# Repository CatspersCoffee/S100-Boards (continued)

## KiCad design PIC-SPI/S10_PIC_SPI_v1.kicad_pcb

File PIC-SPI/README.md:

# PIC-SPI

An S-100 interrupt and SPI board: an 8259A interrupt controller on the bus vectored-interrupt lines, an XC95288XL CPLD driving an SPI bus (DS1305 RTC, two MCP23S08 port expanders) and eight M25P80 SPI flash chips that can be loaded over USB (2016). The project name is `S100 PIC_SPI_v1`; the board carries no title text.

## Status
Built.

## Hardware

| Ref | Part | Role |
|---|---|---|
| U20 | XC95288XL-TQ144 | CPLD: S-100 bus logic, chip selects, SPI master, flash select, 7-segment data |
| U11 | 8259A | Interrupt controller on VI0*–VI7*, output to INT* |
| U22 | DS1305 + X2 + BAT1 (CR2032) | SPI real-time clock with battery backup |
| IC1, IC2 | MCP23S08 | SPI 8-bit port expanders, brought out on P13 "MCP_1" and P14 "MCP_2" |
| U14–U17, U23–U26 | M25P80 ×8 | 8 Mbit SPI flash each, one select line per chip from the CPLD |
| U18 | CH341A (12 MHz X1, USB Jx2) | USB-to-SPI bridge for loading the flash |
| U8 | PIC18F1330 | Switches the flash SPI bus between the CPLD and the CH341A |
| U12 | 74LV244 | Flash SPI bus switch, enabled by the PIC18F1330 |
| U3, U7 | 74LS682 | Address compare against DIP switches SW3 and SW5 (U7 → 8259 select) |
| U21 | 74LS240 | Inverts VI0*–VI7* to the 8259 IR0–IR7 inputs |
| U13 + SW6 | 74LS244 + DIP switch | Interrupt vector byte set by switch, put on the bus by the CPLD |
| U27, U28 + S1, S2 | 74HC4511 ×2 + 7-segment ×2 | Two-digit display driven by the CPLD |
| U4–U6, U19, U31, U3din1, U3dout1, U9, U10 | 74xx541 / 74HC245 | S-100 address, data and status buffers |
| U1, U2, Ux1 | 7805-type LDO, LM1086CS, 3.3 V SOT-223 | +5 V and 3.3 V from the S-100 +8 V rail |

- Board size: 254.0 × 134.1 mm (10.0 × 5.28 in), standard S-100 outline, 2 layers.
- KiCad: 2013-07-07 stable (BZR 4022); `.kicad_pcb` format version 3.
- Headers: P12 "Incomming Interrupt Channels" (jumpers route each VIx* line to 8259 IRx); JPx1–JPx8 "BOARD Interrupt Channel Selector" (picks the VIx* line for the board's own interrupt); JP1 (8259 INT to S-100 INT*); P19 "XILINX CABLE" (JTAG); P5 "PIC ISP"; P1 "FLASH ICP" (GND/CLK/Din/CS/Dout); P3 "EXT SPI"; P2 spare CPLD I/O.
- Switches: SW1 "RESET", SW2 "PIC RESET", SW50 "RUN/PROG"; DIP switches SW3, SW5 (address) and SW6 (interrupt vector).
- LEDs: "RUN", "PROG", "BS" (board select), "D0", "POWER", "POWER CH341A".

## How it works
- The CPLD sits behind buffered S-100 address (A0–A23), data (DI0–DI7, DO0–DO7) and status/control lines (sINP, sOUT, sMEMR, sM1, sINTA, sWO*, pDBIN, pWR*, MWRT, PHI, CLOCK*, RESET*, SLAVE_CLR*).
- Interrupts: incoming VI0*–VI7* reach the 8259A IR inputs through P12 jumpers and a 74LS240; the 8259A INT output goes to S-100 INT* (pin 73) through JP1. The 8259A chip select is decoded by U7 (CPLD pin 69 `in8259CS*`) and driven back out by the CPLD (pin 70 `out8259CS*`).
- The CPLD can also raise its own interrupt (pin 110 `BOARD_INTERRUPT_VECTb`) on any one VIx* line chosen with JPx1–JPx8, and can put a switch-set vector byte (SW6 via U13) on the data bus.
- SPI: CPLD pins 57/58/59 are SPI CLK/Din/Dout to the DS1305, both MCP23S08s and P3. Chip selects come from CPLD pins 25 (DS1305), 26/27 (IC1/IC2) and 17 (P3).
- Flash: the eight M25P80s share one SPI bus with a separate select each (CPLD pins 80–83 and 85–88). The 74LV244 connects that bus either to the CPLD or to the CH341A USB bridge; the PIC18F1330 controls which.
- The CPLD can also drive the S-100 bus-master request lines TMA0*–TMA3* and sXTRQ*.
- No CPLD project for this board is in the backups.

## Files
All files are in this folder:

| File | What it is |
|---|---|
| `S10_PIC_SPI_v1.sch` | Schematic (single sheet) |
| `S10_PIC_SPI_v1-cache.lib` | Symbol cache for the schematic |
| `S10_PIC_SPI_v1.kicad_pcb` | PCB layout |
| `S10_PIC_SPI_v1.net` | Netlist |
| `S10_PIC_SPI_v1.cmp` | Footprint assignments |
| `S10_PIC_SPI_v1.pro` | KiCad project |

## History
The git history replays the original dated KiCad backups, 3–10 January 2016. The first commit is the Flash-UART layout with its tracks removed, and the Flash-UART netlist and footprint files are carried over unchanged.

## Things to check (TODO)
- The P2 header silkscreen labels (P71–P78, P110–P116) are Flash-UART net names; on this board those pins go to CPLD pins 105–100 and 93–98.
- The final layout reports 1 unrouted connection.

## Credits
- Started from the user's own [Flash-UART](../Flash-UART) design.
- The S-100 edge connector symbol (`S100_MALE`) comes from the N8VEM KiCad library.
- John Monahan's 8259A test programs for his S100Computers.com PIC/RTC board (2010) were kept in the original project folder as reference. They are not included here.

## License
Hardware: CERN-OHL-S-2.0 for the original work in this folder; see the repo NOTICE for third-party parts.

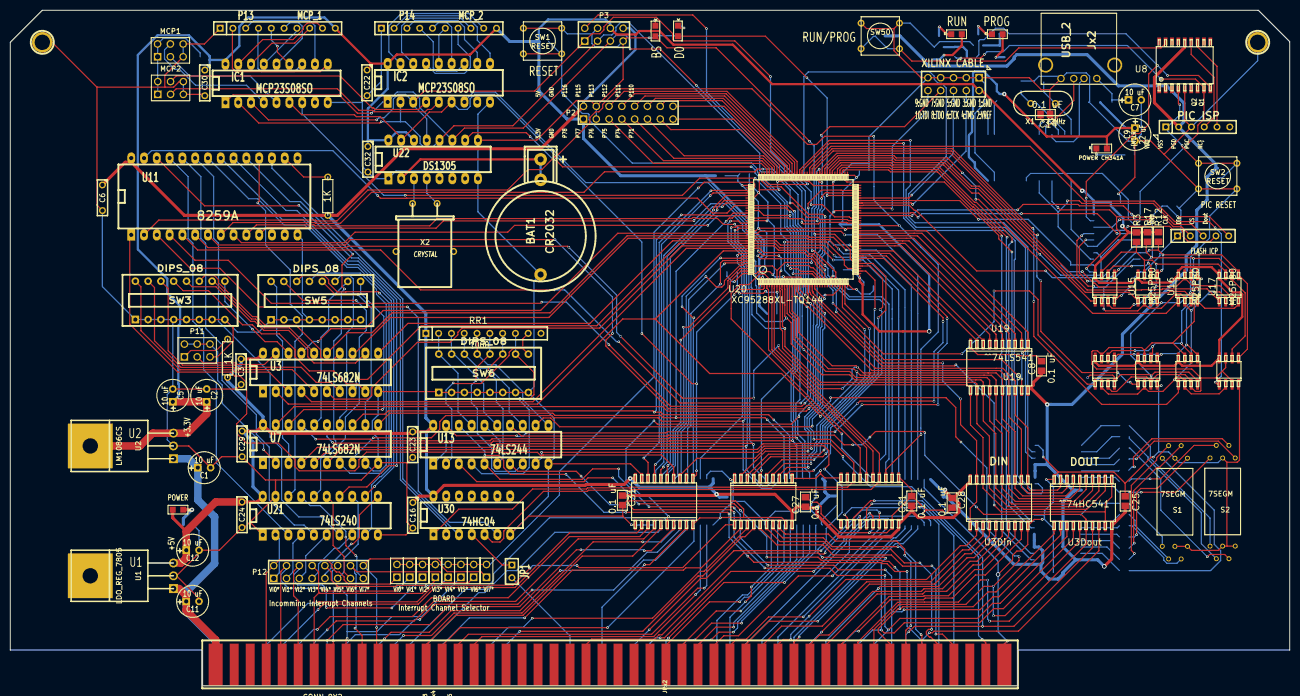
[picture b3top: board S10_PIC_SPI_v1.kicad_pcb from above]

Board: 2 copper layers, 254.0 x 134.1 mm, 163 parts (0 on the bottom side), 326 nets.

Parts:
BAT1: CR2032; ^^CR2032H
C1, C2, C5, C7, C11, C12: 10 uF; C1V7
C3, C6, C16, C22, C23, C24, C29, C30, C32: 0.1 uF; C2
C4, C8, C14, C17, C20, C21, C25, C27, C28, C31, C41, C42, C43: 0.1 uF; ^^SMD_Resistor-0805
C9: 22 uF; C1V7
C10, C18: 15 pF; ^^SMD_Resistor-0805
C13, C15: 0.01 uF; ^^SMD_Resistor-0805
C19, C26, C33, C34, C35, C36, C37, C38, C39, C40: C; ^^SMD_Resistor-0805
D1, D4: LED; ^^LED-0805
D5: POWER; ^^LED-0805
D7: BOARD_SELECT; ^^LED-0805
D8: POWER CH341A; ^^LED-0805
D9: D0; ^^LED-0805
IC1, IC2: MCP23S08SO; DIP-18__300_ELL
JP1: JUMPER; SIL-2
JPx1, JPx2, JPx3, JPx4, JPx5, JPx6, JPx7, JPx8: JUMPER; PIN_ARRAY_2X1
Jx2: USB_2; USB_A
MCP1, MCP2: CONN_3X2; PIN_ARRAY_3X2
P1: M25P80 ISP; SIL-5
P2: CONN_8X2; PIN_ARRAY_8x2
P3: EXT SPI; PIN_ARRAY_4X2
P4: S100_MALE
P5: PIC_ISP; SIL-6
P6, P7: CONN_1; 1pin
P8, P9: CONN_2; ^^SMD_Resistor-0805
P11: CONN_3X2; PIN_ARRAY_3X2
P12: CONN_8X2; pin_array_8x2
P13: MCP_1; SIL-10
P14: MCP_2; SIL-10
P19: XILINX CABLE2; PIN_ARRAY_5x2
Q1, Q2: ^^NPN-SOT23; ^^-SOT23
R1, R5, R14, R15, R20, R21, R29: 330; ^^SMD_Resistor-0805
R2, R18, R19, R28: 470; ^^SMD_Resistor-0805
R3, R31, R32, R33, R34, R35, R36, R37, R38, R39, R40, R41, R42, R43, R44: 1K; ^^SMD_Resistor-0805
R4, R8, R10, R30: 10k; ^^SMD_Resistor-0805
R6, R11: 1K; ^^R3
R7: 50; ^^SMD_Resistor-0805
R9, R12, R17: 10K; ^^SMD_Resistor-0805
R25, R26, R27: 100; ^^SMD_Resistor-0805
RR1: 1000; r_pack9
S1, S2: 7SEGM; ^^VQB71_7segment
SW1, SW2: RESET; SW_PUSH_SMALL
SW3, SW5, SW6: DIPS_08; SWDIP8
SW50: FLASH/RUN; SW_PUSH_SMALL
U1: LDO_REG_7805; ^^TO220
U2: LM1086CS; ^^TO220
U3, U7: 74LS682N; DIP-20__300_ELL
U3din1, U3dout1: ^^74HC541; ^^-SO20W
U4, U5, U6, U19, U31: ^^74LS541; ^^-SO20W
U8: PIC18F1330; -SO18-1
U9, U10: 74HC245; ^^-SO20W
U11: 8259A; DIP-28__600_ELL
U12: ^^74LV244; ^^-SO20W
U13: 74LS244; DIP-20__300_ELL
U14, U15, U16, U17, U23, U24, U25, U26: M25P80; -SO8
U18: CH341A; ^^-SO28W
U20: XC95288XL-TQ144; -TQFP144
U21: 74LS240; DIP-20__300_ELL
U22: DS1305; DIP-16__300_ELL
U27, U28: 74HC4511; ^^-SO16W
U30: 74HC04; DIP-14__300_ELL
Ux1: ^^3.3VREG_SOT223; -SOT223
X1: 12MHz; Crystal_HC-49U_Vert
X2: CRYSTAL; Crystal_HC-49U_Horiz

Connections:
/7SEG_0_D0: U20.74, U27.7
/7SEG_0_D1: U20.75, U27.1
/7SEG_0_D2: U20.76, U27.2
/7SEG_0_D3: U20.77, U27.6
/7SEG_1_D0: U20.106, U28.7
/7SEG_1_D1: U20.107, U28.1
/7SEG_1_D2: U20.91, U28.2
/7SEG_1_D3: U20.92, U28.6
/25Pxx_CS: U12.5, U12.14, U20.79
/25Pxx_SEL_0: U14.1, U20.80
/25Pxx_SEL_1: U15.1, U20.81
/25Pxx_SEL_2: U16.1, U20.82
/25Pxx_SEL_3: U17.1, U20.83
/25Pxx_SEL_4: U20.85, U23.1
/25Pxx_SEL_5: U20.86, U24.1
/25Pxx_SEL_6: U20.87, U25.1
/25Pxx_SEL_7: U20.88, U26.1
/+8V: C1.1, C11.1, P4.1, P4.51, U1.1, U2.1
//M1: U9.2, U20.43
/A0: P4.79, U4.2
/A0b: U4.18, U11.27, U20.117
/A1: P4.80, U4.3
/A1b: U4.17, U7.17, U20.118
/A2: P4.81, U4.4
/A2b: U4.16, U7.15, U20.119
/A3: P4.31, U4.5
/A3b: U4.15, U7.13, U20.120
/A4: P4.30, U4.6
/A4b: U4.14, U7.11, U20.121
/A5: P4.29, U4.7
/A5b: U4.13, U7.8, U20.124
/A6: P4.82, U4.8
/A6b: U4.12, U7.6, U20.125
/A7: P4.83, U4.9
/A7b: U4.11, U7.4, U20.126
/A8: P4.84, U5.2
/A8b: U3.17, U5.18, U20.128
/A9: P4.34, U5.3
/A9b: U3.15, U5.17, U20.129
/A10: P4.37, U5.4
/A10b: U3.13, U5.16, U20.130
/A11: P4.87, U5.5
/A11b: U3.11, U5.15, U20.131
/A12: P4.33, U5.6
/A12b: U3.8, U5.14, U20.132
/A13: P4.85, U5.7
/A13b: U3.6, U5.13, U20.133
/A14: P4.86, U5.8
/A14b: U3.4, U5.12, U20.134
/A15: P4.32, U5.9
/A15b: U3.2, U5.11, U20.135
/A16: P4.16, U6.2
/A16b: U6.18, U20.136
/A17: P4.17, U6.3
/A17b: U6.17, U20.137
/A18: P4.15, U6.4
/A18b: U6.16, U20.138
/A19: P4.59, U6.5
/A19b: U6.15, U20.139
/A20: P4.61, U6.6
/A20b: U6.14, U20.140
/A21: P4.62, U6.7
/A21b: U6.13, U20.142
/A22: P4.63, U6.8
/A22b: U6.12, U20.143
/A23: P4.64, U6.9
/A23b: U6.11, U20.116
/BOARD_INTERRUPT_VECTb: JPx1.2, JPx2.2, JPx3.2, JPx4.2, JPx5.2, JPx6.2, JPx7.2, JPx8.2, U20.110
/BOARD_SEL_LED: D7.1, U20.31
/CLOCK*: P4.49, U10.13
/CLOCK*b: U10.7, U20.5
/CPLD2_TCK: R25.1, U20.67
/CPLD2_TDI: R26.1, U20.63
/CPLD2_TDO: P19.8, U20.122
/CPLD2_TMS: R27.1, U20.65
/CPLD_45: U19.9, U20.45
/CPLD_46: U19.8, U20.46
/CPLD_48: U19.7, U20.48
/CPLD_49: U19.6, U20.49
/CPLD_68: D9.1, U20.68
/CPLD_71: P2.15, U20.100
/CPLD_74: P2.13, U20.101
/CPLD_75: P2.11, U20.102
/CPLD_76: P2.9, U20.103
/CPLD_77: P2.7, U20.104
/CPLD_78: P2.5, U20.105
/CPLD_110: P2.16, U20.98
/CPLD_111: P2.14, U20.97
/CPLD_112: P2.12, U20.96
/CPLD_113: P2.10, U20.95
/CPLD_115: P2.8, U20.94
/CPLD_116: P2.6, U20.93
/CPLD_130: U19.5, U20.50
/CPLD_131: U19.4, U20.51
/CPLD_132: U19.3, U20.52
/CPLD_133: U19.2, U20.53
/CPLD_134: U19.1, U19.19, U20.54
/CPLD_M25P80_CLK: U12.2, U20.60
/CPLD_M25P80_CS: U12.6, U20.64
/CPLD_M25P80_Din: U12.4, U20.61
/CPLD_M25P80_Dout: R9.2, U12.12, U20.66
/D0: U3din1.18, U3dout1.2, U11.11, U19.11, U20.9
/D1: U3din1.17, U3dout1.3, U11.10, U19.12, U20.10
/D2: U3din1.16, U3dout1.4, U11.9, U19.13, U20.11
/D3: U3din1.15, U3dout1.5, U11.8, U19.14, U20.12
/D4: U3din1.14, U3dout1.6, U11.7, U19.15, U20.13
/D5: U3din1.13, U3dout1.7, U11.6, U19.16, U20.14
/D6: U3din1.12, U3dout1.8, U11.5, U19.17, U20.15
/D7: U3din1.11, U3dout1.9, U11.4, U19.18, U20.16
/DBUSIN_EN: U3din1.1, U3din1.19, U20.22
/DBUSOUT_EN: U3dout1.1, U3dout1.19, U20.21
/DI0: P4.95, U3dout1.18, U13.18
/DI1: P4.94, U3dout1.17, U13.16
/DI2: P4.41, U3dout1.16, U13.14
/DI3: P4.42, U3dout1.15, U13.12
/DI4: P4.91, U3dout1.14, U13.9
/DI5: P4.92, U3dout1.13, U13.7
/DI6: P4.93, U3dout1.12, U13.5
/DI7: P4.43, U3dout1.11, U13.3
/DO0: P4.36, U3din1.2
/DO1: P4.35, U3din1.3
/DO2: P4.88, U3din1.4
/DO3: P4.89, U3din1.5
/DO4: P4.38, U3din1.6
/DO5: P4.39, U3din1.7
/DO6: P4.40, U3din1.8
/DO7: P4.90, U3din1.9
/INT*: JP1.2, P4.73
/IOREQb: P4.69, U9.14
/IOREQbb: U9.6, U20.39
/M2_MCLR: P5.1, R4.2, SW2.1, U8.4
/M2_PGC: P5.5, U8.12
/M2_PGD: P5.4, U8.13
/MCP1_0: IC1.10, P13.2
/MCP1_1: IC1.11, P13.3
/MCP1_2: IC1.12, P13.4
/MCP1_3: IC1.13, P13.5
/MCP1_4: IC1.14, P13.6
/MCP1_5: IC1.15, P13.7
/MCP1_6: IC1.16, P13.8
/MCP1_7: IC1.17, P13.9
/MCP2_0: IC2.10, P14.2
/MCP2_1: IC2.11, P14.3
/MCP2_2: IC2.12, P14.4
/MCP2_3: IC2.13, P14.5
/MCP2_4: IC2.14, P14.6
/MCP2_5: IC2.15, P14.7
/MCP2_6: IC2.16, P14.8
/MCP2_7: IC2.17, P14.9
/MCP_AddrHi: MCP1.1, MCP1.2, MCP2.1, MCP2.2, R7.1
/MWRT: P4.68, U9.13
/MWRTb: U9.7, U20.40
/NDEF2: P4.65, U9.12
/NDEF2b: U9.8, U20.41
/PHI: P4.24, U10.14
/PHIb: U10.6, U20.4
/PROG_M25P80_CLK: P1.2, U12.11, U18.18
/PROG_M25P80_CS: P1.4, U12.15, U18.15
/PROG_M25P80_Din: P1.3, U12.13, U18.20
/PROG_M25P80_Dout: P1.5, R10.2, U12.3, U18.22
/Q1: R2.2, R18.2, U8.9, U12.19
/Q2: R19.2, R28.2, U8.8, U12.1
/RESET*: P4.75, U31.9
/RESET*b: IC1.6, IC2.6, U20.3, U22.15, U31.11
/SLAVE_CLR*: P4.54, U9.11
/SLAVE_CLR*vv: U9.9, U20.33
/SPI_CLK: IC1.1, IC2.1, P3.5, U20.57, U22.11
/SPI_CS_00: U20.25, U22.10
/SPI_CS_01: IC1.7, U20.26
/SPI_CS_02: IC2.7, U20.27
/SPI_CS_03: P3.2, U20.17
/SPI_Din: IC1.2, IC2.2, P3.3, U20.58, U22.12
/SPI_Dout: IC1.3, IC2.3, P3.1, U20.59, U22.13
/TMA0*: P4.55, U31.2
/TMA0_CPLD: U20.111, U31.18
/TMA1*: P4.56, U31.3
/TMA1_CPLD: U20.112, U31.17
/TMA2*: P4.57, U31.4
/TMA2_CPLD: U20.113, U31.16
/TMA3*: P4.14, U31.5
/TMA3_CPLD: U20.115, U31.15
/USB_VCC1: C7.1, Jx2.1, Ux1.3
/V3.3: C2.1, C4.1, C5.1, C22.1, C30.1, C32.1, IC1.18, IC2.18, P2.1, P3.6, P8.2, P9.2, P13.10, P14.10, P19.2, R3.2, R7.2, R8.1, R12.1, R17.1, U2.3, U2.4, U12.20, U14.8, U15.8, U16.8, U17.8, U22.14, U22.16, U23.8, U24.8, U25.8, U26.8
/V3.3_CLPD_INT: C26.1, C33.1, P8.1, U20.8, U20.42, U20.84, U20.141
/V3.3_CLPD_IO: C19.1, C34.1, C35.1, C36.1, C37.1, C38.1, C39.1, C40.1, P9.1, U20.1, U20.37, U20.55, U20.73, U20.109, U20.127
/V3.3b: C9.1, C13.2, C15.1, D8.1, U18.28, Ux1.2
/VI0: U11.18, U21.18
/VI0*: JPx1.1, P4.4, P12.2
/VI1: U11.19, U21.16
/VI1*: JPx2.1, P4.5, P12.4
/VI2: U11.20, U21.14
/VI2*: JPx3.1, P4.6, P12.6
/VI3: U11.21, U21.12
/VI3*: JPx4.1, P4.7, P12.8
/VI4: U11.22, U21.9
/VI4*: JPx5.1, P4.8, P12.10
/VI5: U11.23, U21.7
/VI5*: JPx6.1, P4.9, P12.12
/VI6: U11.24, U21.5
/VI6*: JPx7.1, P4.10, P12.14
/VI7: U11.25, U21.3
/VI7*: JPx8.1, P4.11, P12.16
/Vbat: BAT1.1, U22.2
/Z80intVectorBusout: U13.1, U13.19, U20.44
/in8259CS*: U7.19, U20.69
/out8259CS*: U20.70, U31.6
/out8259CS*bufferedViaU31: U11.1, U31.14
/pDBIN: P4.78, U10.16
/pDBIN*b: U11.3, U30.6
/pDBINb: U10.4, U20.7, U30.5
/pWR*: P4.77, U10.17
/pWR*b: U10.3, U11.2, U20.56
/sINP: P4.46, U9.16
/sINPb: U9.4, U20.35
/sINTA: P4.96, U10.12
/sINTA*b: U11.26, U30.2
/sINTAb: U10.8, U20.20, U30.1
/sM1: P4.44, U9.18
/sMEMR: P4.47, U9.15
/sMEMRb: U9.5, U20.38
/sOUT: P4.45, U9.17
/sOUTb: U9.3, U20.34
/sWO*: P4.97, U10.15
/sWO*b: U10.5, U20.6
/sXTRQ*: P4.58, U31.7
/sXTRQ*b: U20.23, U31.13
GND: BAT1.2, C1.2, C2.2, C3.2, C4.2, C5.2, C6.2, C7.2, C8.2, C9.2, C10.2, C11.2, C12.2, C14.1, C15.2, C16.2, C17.2, C18.2, C19.2, C20.2, C21.2, C22.2, C23.2, C24.2, C25.2, C26.2, C27.2, C28.2, C29.2, C30.2, C31.2, C32.2, C33.2, C34.2, C35.2, C36.2, C37.2, C38.2, C39.2, C40.2, C41.2, C42.2, C43.2, IC1.9, IC2.9, Jx2.4, MCP1.5, MCP1.6, MCP2.5, MCP2.6, P1.1, P2.3, P2.4, P3.4, P3.7, P4.50, P4.100, P5.3, P6.1, P7.1, P11.5, P13.1, P14.1, P19.1, P19.3, P19.5, P19.7, P19.9, Q1.2, Q2.2, R5.2, R9.1, R10.1, R14.2, R15.1, R20.1, R21.1, S1.3, S1.5, S1.8, S2.3, S2.5, S2.8, SW1.1, SW2.2, SW3.1, SW3.2, SW3.3, SW3.4, SW3.5, SW3.6, SW3.7, SW3.8, SW5.1, SW5.2, SW5.3, SW5.4, SW5.5, SW5.6, SW5.7, SW5.8, SW6.1, SW6.2, SW6.3, SW6.4, SW6.5, SW6.6, SW6.7, SW6.8, SW50.1, U1.2, U2.2, U3.10, U3din1.10, U3dout1.10, U4.1, U4.10, U4.19, U5.1, U5.10, U5.19, U6.1, U6.10, U6.19, U7.10, U8.5, U9.1, U9.10, U9.19, U10.1, U10.10, U10.19, U11.14, U12.10, U13.10, U14.4, U15.4, U16.4, U17.4, U18.12, U18.27, U19.10, U20.18, U20.29, U20.36, U20.47, U20.62, U20.72, U20.89, U20.90, U20.99, U20.108, U20.114, U20.123, U20.144, U21.1, U21.10, U21.19, U22.1, U22.8, U22.9, U23.4, U24.4, U25.4, U26.4, U27.8, U28.8, U30.7, U31.1, U31.10, U31.19, Ux1.1
unnamed: P12.7, U21.8
unnamed: P12.9, U21.11
unnamed: P12.11, U21.13
unnamed: P12.13, U21.15
unnamed: P12.15, U21.17
unnamed: P12.5, U21.6
unnamed: P12.1, U21.2
unnamed: P12.3, U21.4
unnamed: RR1.5, SW6.13, U13.11
unnamed: RR1.4, SW6.14, U13.13
unnamed: RR1.3, SW6.15, U13.15
unnamed: P11.3, U3.19
unnamed: RR1.7, SW6.11, U13.6
unnamed: RR1.8, SW6.10, U13.4
unnamed: RR1.6, SW6.12, U13.8
unnamed: RR1.2, SW6.16, U13.17
unnamed: RR1.9, SW6.9, U13.2
unnamed: SW3.11, U3.14
unnamed: SW3.12, U3.12
unnamed: SW3.13, U3.9
unnamed: SW3.14, U3.7
unnamed: SW3.15, U3.5
unnamed: SW3.16, U3.3
unnamed: SW3.10, U3.16
unnamed: SW3.9, U3.18
unnamed: JP1.1, U30.4
unnamed: IC2.4, MCP2.4
unnamed: IC1.5, MCP1.3
unnamed: IC1.4, MCP1.4
unnamed: IC2.5, MCP2.3
unnamed: SW5.9, U7.18
unnamed: SW5.10, U7.16
unnamed: SW5.11, U7.14
unnamed: SW5.12, U7.12
unnamed: SW5.13, U7.9
unnamed: SW5.14, U7.7
unnamed: SW5.15, U7.5
unnamed: SW5.16, U7.3
unnamed: U22.3, X2.1
unnamed: U22.4, X2.2
unnamed: P11.2, P11.4, P11.6, U7.2
unnamed: D1.2, Q1.3
unnamed: D9.2, R21.2
unnamed: D4.2, Q2.3
unnamed: Jx2.3, U18.10
unnamed: C10.1, U18.13, X1.1
unnamed: C18.1, U18.14, X1.2
unnamed: Jx2.2, U18.11
unnamed: R15.2, U18.1
unnamed: D8.2, R14.1
unnamed: R8.2, SW1.2, U20.24
unnamed: R36.1, S1.9
unnamed: R31.1, S1.7
unnamed: R32.1, S1.6
unnamed: R33.1, S1.4
unnamed: R34.1, S1.2
unnamed: R35.1, S1.1
unnamed: R37.1, S1.10
unnamed: R38.1, S2.7
unnamed: R39.1, S2.6
unnamed: R40.1, S2.4
unnamed: R41.1, S2.2
unnamed: R42.1, S2.1
unnamed: R43.1, S2.9
unnamed: R44.1, S2.10
unnamed: R42.2, U28.9
unnamed: R37.2, U27.14
unnamed: R31.2, U27.13
unnamed: R32.2, U27.12
unnamed: R33.2, U27.11
unnamed: R34.2, U27.10
unnamed: R35.2, U27.9
unnamed: R36.2, U27.15
unnamed: R38.2, U28.13
unnamed: R39.2, U28.12
unnamed: R40.2, U28.11
unnamed: R41.2, U28.10
unnamed: R43.2, U28.15
unnamed: R44.2, U28.14
unnamed: D7.2, R20.2
unnamed: C14.2, U18.9
unnamed: C13.1, U18.2
unnamed: P11.1, R11.2
unnamed: U11.17, U30.3
unnamed: R6.1, U11.16
unnamed: D1.1, R1.1
unnamed: R3.1, U14.3, U14.7, U15.3, U15.7, U16.3, U16.7, U17.3, U17.7, U23.3, U23.7, U24.3, U24.7, U25.3, U25.7, U26.3, U26.7
unnamed: D4.1, R29.1
unnamed: P19.10, R26.2
unnamed: P19.6, R25.2
unnamed: P19.4, R27.2
unnamed: D5.2, R5.1
unnamed: R30.2, SW50.2, U8.17
unnamed: R17.2, U12.9, U12.18, U14.6, U15.6, U16.6, U17.6, U23.6, U24.6, U25.6, U26.6
unnamed: Q1.1, R2.1, R19.1
unnamed: Q2.1, R18.1, R28.1
unnamed: R12.2, U12.7, U12.16, U14.5, U15.5, U16.5, U17.5, U23.5, U24.5, U25.5, U26.5
unnamed: U12.8, U12.17, U14.2, U15.2, U16.2, U17.2, U23.2, U24.2, U25.2, U26.2
VCC: C3.1, C6.1, C8.1, C12.1, C16.1, C17.1, C20.1, C21.1, C23.1, C24.1, C25.1, C27.1, C28.1, C29.1, C31.1, C41.1, C42.1, C43.1, D5.1, P2.2, P3.8, P5.2, R1.2, R4.1, R6.2, R11.1, R29.2, R30.1, RR1.1, U1.3, U3.20, U3din1.20, U3dout1.20, U4.20, U5.20, U6.20, U7.20, U8.14, U9.20, U10.20, U11.28, U13.20, U19.20, U21.20, U27.3, U27.4, U27.5, U27.16, U28.3, U28.4, U28.5, U28.16, U30.14, U31.20

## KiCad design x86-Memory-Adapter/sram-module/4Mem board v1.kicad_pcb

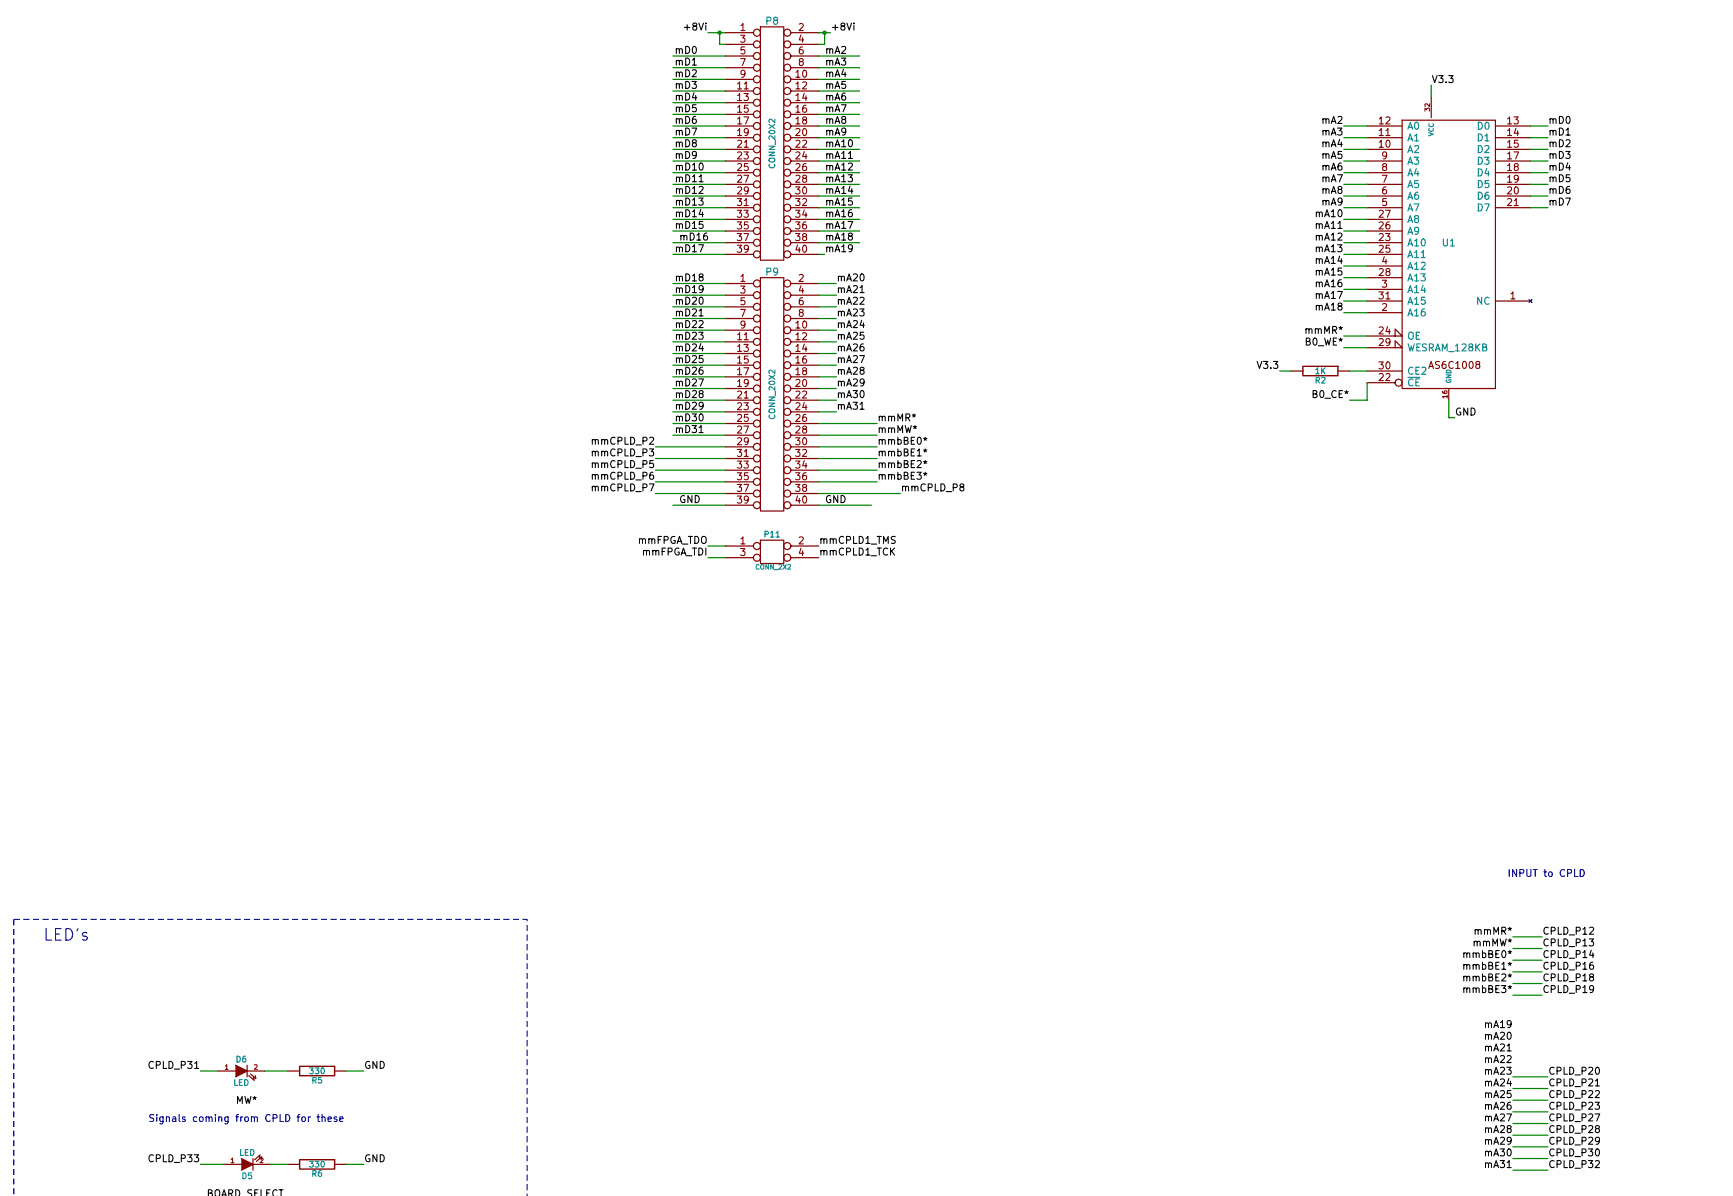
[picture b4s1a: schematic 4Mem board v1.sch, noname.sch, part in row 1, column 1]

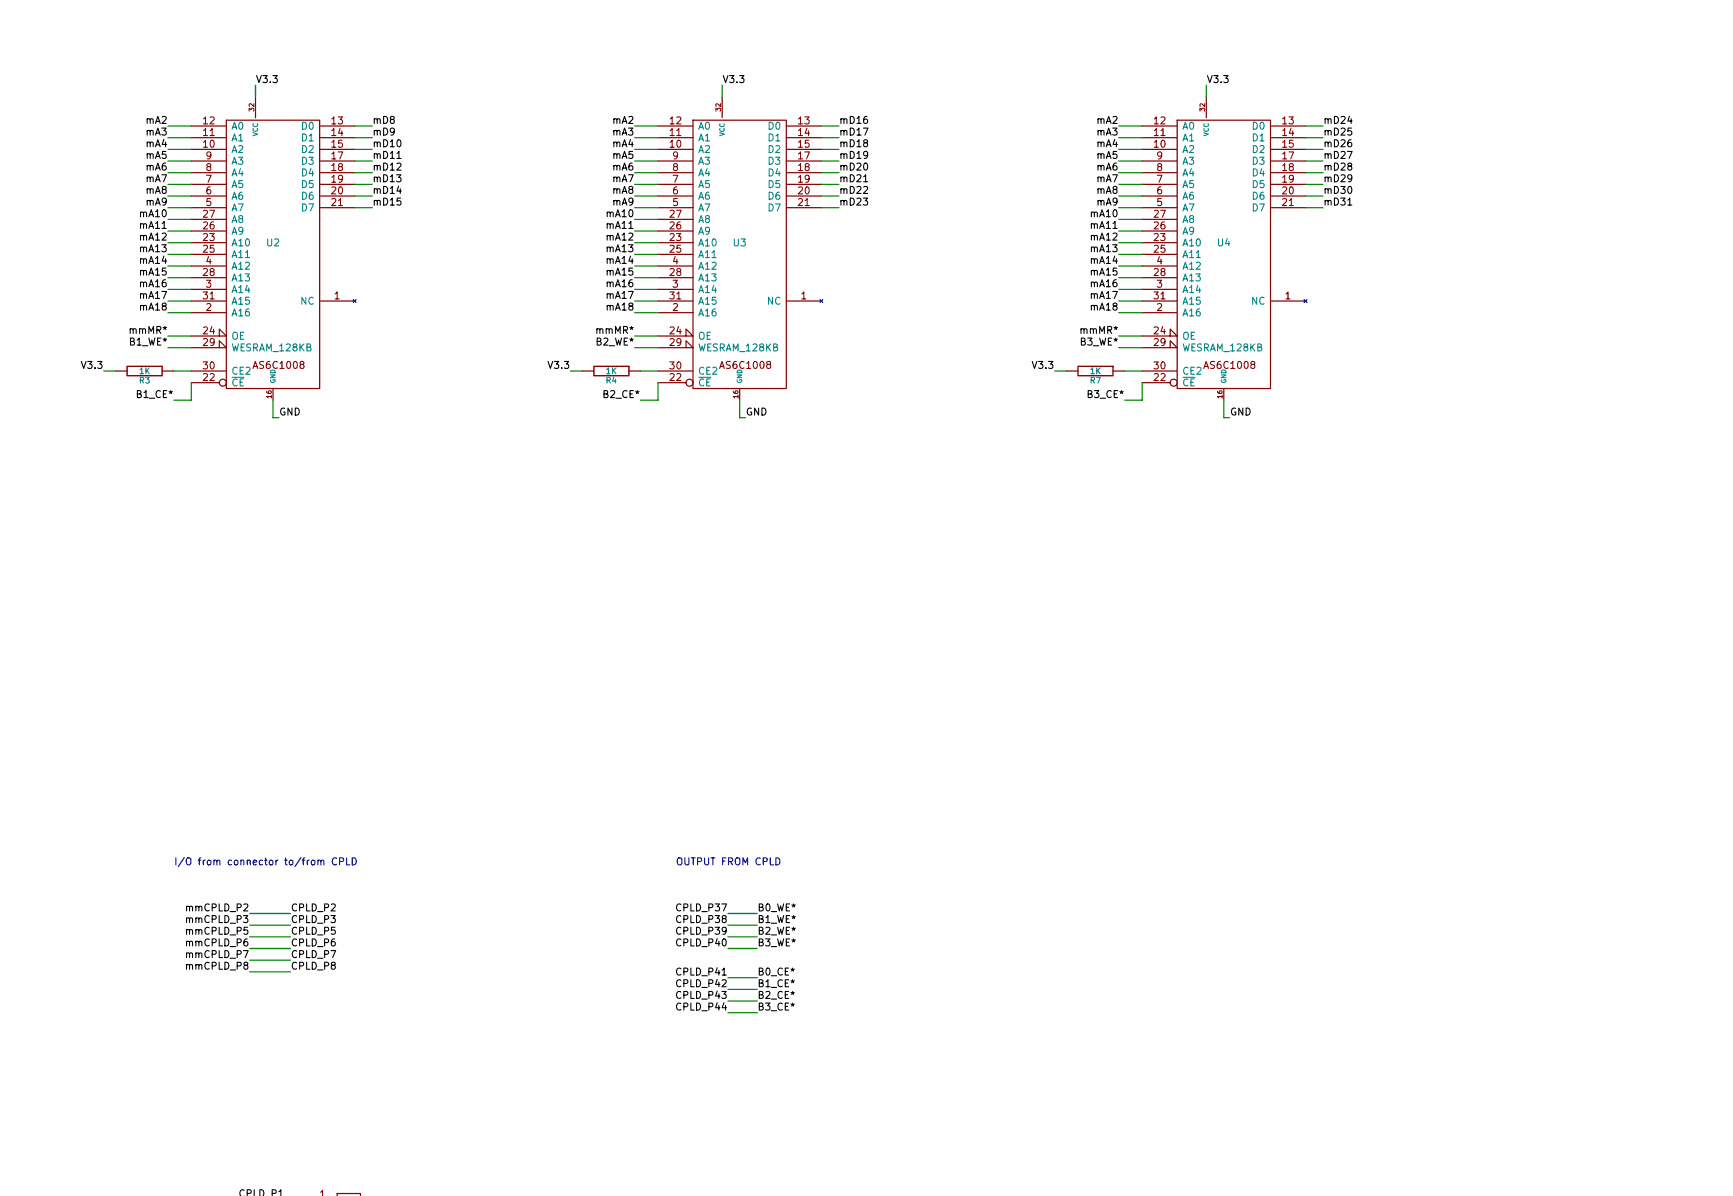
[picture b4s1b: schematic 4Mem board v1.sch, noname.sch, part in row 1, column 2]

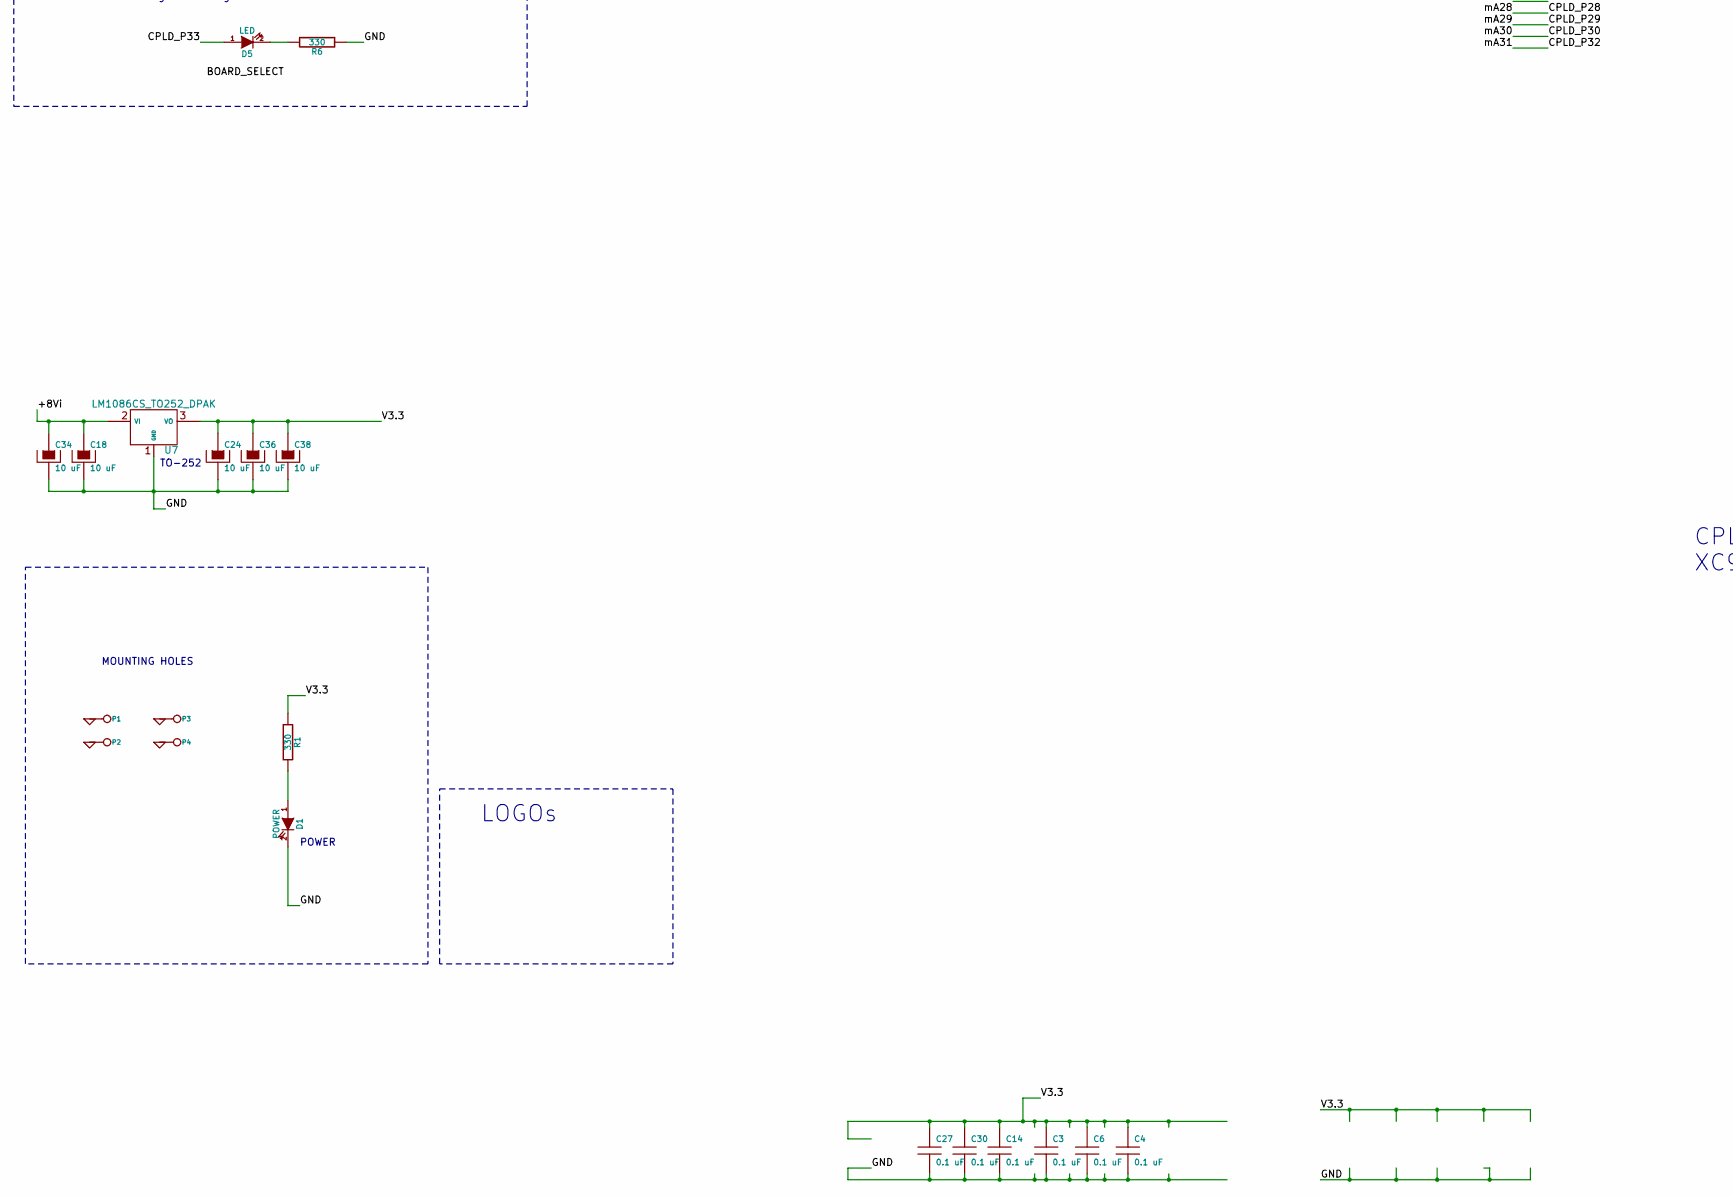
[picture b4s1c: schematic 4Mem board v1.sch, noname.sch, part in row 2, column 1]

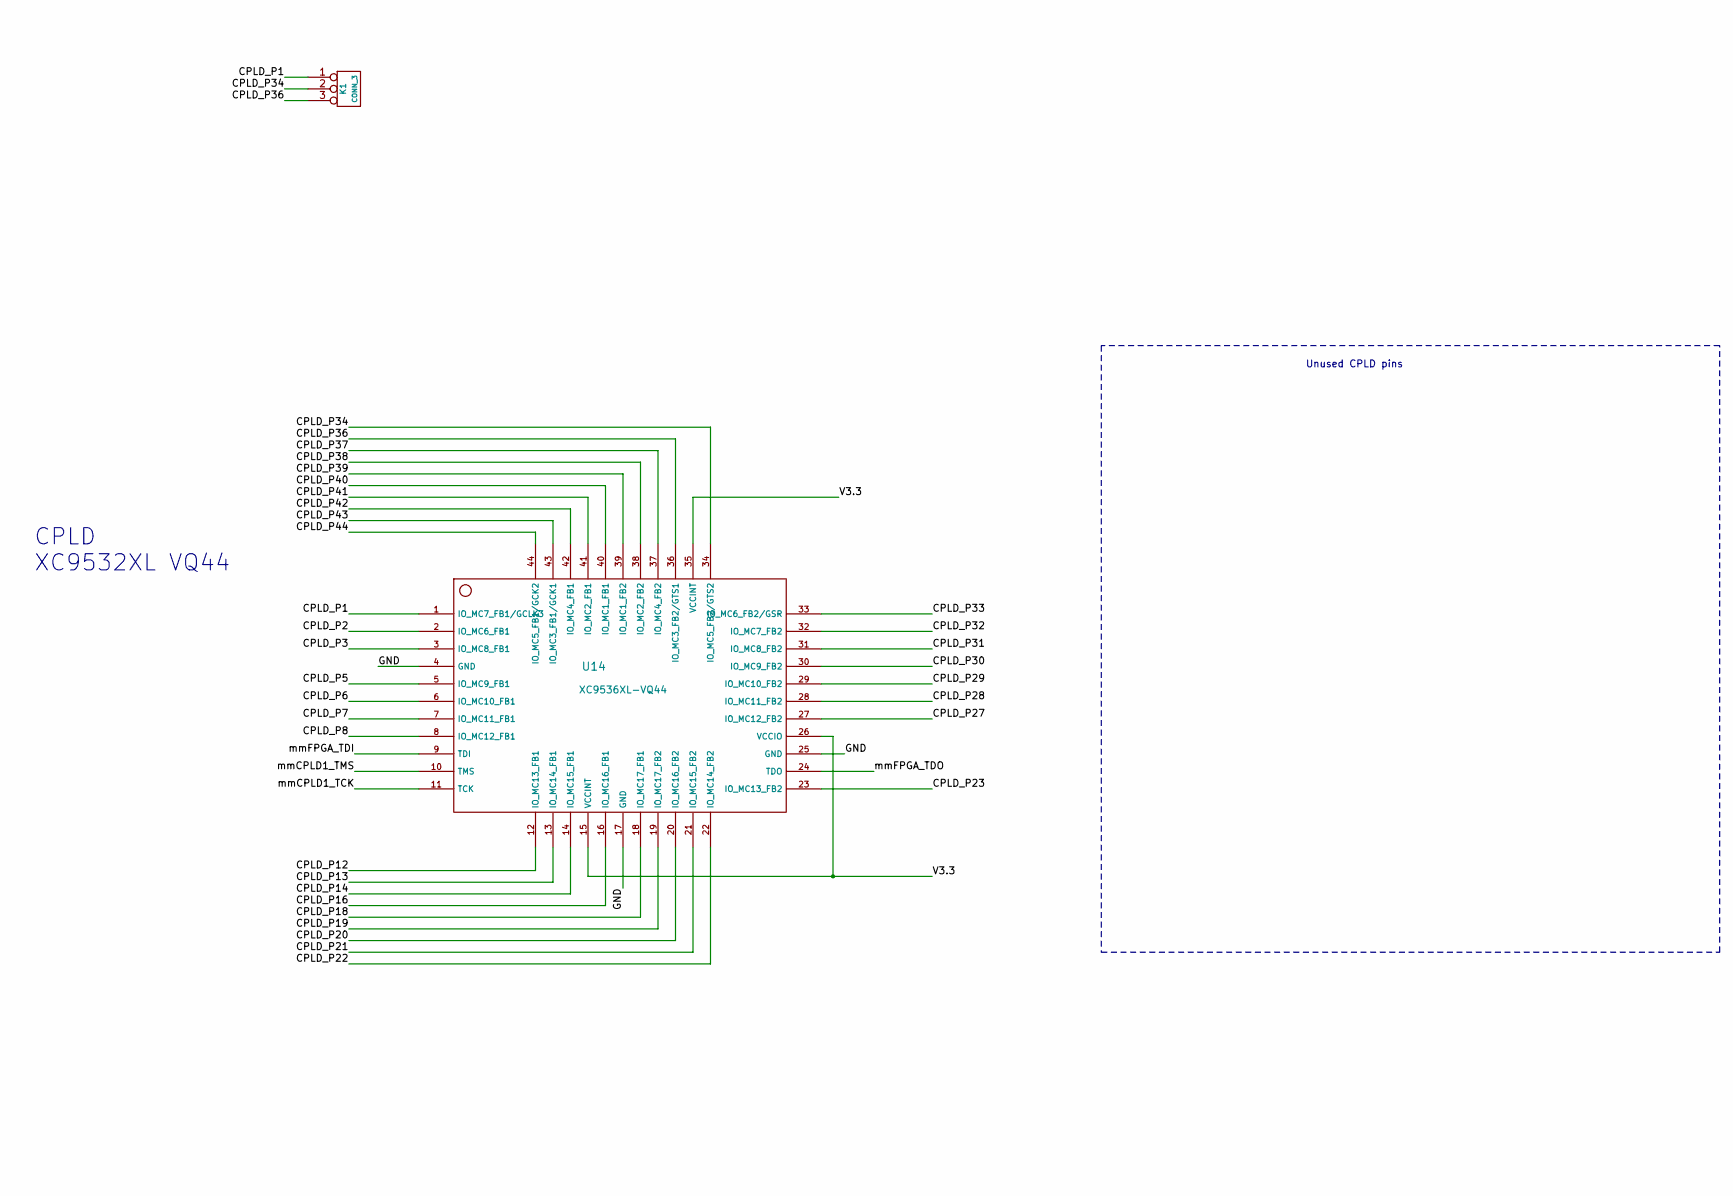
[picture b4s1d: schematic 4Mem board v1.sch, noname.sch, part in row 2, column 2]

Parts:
C3, C4, C6, C14: 0.1 uF; C2
C18, C24, C34, C36, C38: 10 uF
C27, C30: 0.1 uF
D1: POWER
D5, D6: LED; LEDV
K1: CONN_3
P1, P2, P3, P4: CONN_1
P8, P9: CONN_20X2; 8MB_SRAM
P11: CONN_2X2
R1, R5, R6: 330
R2, R3, R4, R7: 1K
U1, U2, U3, U4: SRAM_128KB
U7: LM1086CS_TO252_DPAK
U14: XC9536XL-VQ44

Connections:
/+8Vi: C18.1, C34.1, P8.1, P8.2, P8.3, P8.4, U7.2 (VI)
/B0_CE*: U1.22 (~CE), U14.41 (IO_MC2_FB1)
/B0_WE*: U1.29 (WE), U14.37 (IO_MC4_FB2)
/B1_CE*: U2.22 (~CE), U14.42 (IO_MC4_FB1)
/B1_WE*: U2.29 (WE), U14.38 (IO_MC2_FB2)
/B2_CE*: U3.22 (~CE), U14.43 (IO_MC3_FB1/GCK1)
/B2_WE*: U3.29 (WE), U14.39 (IO_MC1_FB2)
/B3_CE*: U4.22 (~CE), U14.44 (IO_MC5_FB1/GCK2)
/B3_WE*: U4.29 (WE), U14.40 (IO_MC1_FB1)
/CPLD_P1: K1.1, U14.1 (IO_MC7_FB1/GCLK3)
/CPLD_P2: P9.29, U14.2 (IO_MC6_FB1)
/CPLD_P3: P9.31, U14.3 (IO_MC8_FB1)
/CPLD_P5: P9.33, U14.5 (IO_MC9_FB1)
/CPLD_P6: P9.35, U14.6 (IO_MC10_FB1)
/CPLD_P7: P9.37, U14.7 (IO_MC11_FB1)
/CPLD_P8: P9.38, U14.8 (IO_MC12_FB1)
/CPLD_P12: P9.26, U1.24 (OE), U2.24 (OE), U3.24 (OE), U4.24 (OE), U14.12 (IO_MC13_FB1)
/CPLD_P13: P9.28, U14.13 (IO_MC14_FB1)
/CPLD_P14: P9.30, U14.14 (IO_MC15_FB1)
/CPLD_P16: P9.32, U14.16 (IO_MC16_FB1)
/CPLD_P18: P9.34, U14.18 (IO_MC17_FB1)
/CPLD_P19: P9.36, U14.19 (IO_MC17_FB2)
/CPLD_P20: P9.8, U14.20 (IO_MC16_FB2)
/CPLD_P21: P9.10, U14.21 (IO_MC15_FB2)
/CPLD_P22: P9.12, U14.22 (IO_MC14_FB2)
/CPLD_P23: P9.14, U14.23 (IO_MC13_FB2)
/CPLD_P27: P9.16, U14.27 (IO_MC12_FB2)
/CPLD_P28: P9.18, U14.28 (IO_MC11_FB2)
/CPLD_P29: P9.20, U14.29 (IO_MC10_FB2)
/CPLD_P30: P9.22, U14.30 (IO_MC9_FB2)
/CPLD_P31: D6.1 (A), U14.31 (IO_MC8_FB2)
/CPLD_P32: P9.24, U14.32 (IO_MC7_FB2)
/CPLD_P33: D5.1 (A), U14.33 (IO_MC6_FB2/GSR)
/CPLD_P34: K1.2 (PM), U14.34 (IO_MC5_FB2/GTS2)
/CPLD_P36: K1.3, U14.36 (IO_MC3_FB2/GTS1)
/V3.3: C3.1, C4.1, C6.1, C14.1, C24.1, C27.1, C30.1, C36.1, C38.1, R1.1, R2.2, R3.2, R4.2, R7.2, U1.32 (VCC), U2.32 (VCC), U3.32 (VCC), U4.32 (VCC), U7.3 (VO), U14.15 (VCCINT), U14.26 (VCCIO), U14.35 (VCCINT)
/mA2: P8.6, U1.12 (A0), U2.12 (A0), U3.12 (A0), U4.12 (A0)
/mA3: P8.8, U1.11 (A1), U2.11 (A1), U3.11 (A1), U4.11 (A1)
/mA4: P8.10, U1.10 (A2), U2.10 (A2), U3.10 (A2), U4.10 (A2)
/mA5: P8.12, U1.9 (A3), U2.9 (A3), U3.9 (A3), U4.9 (A3)
/mA6: P8.14, U1.8 (A4), U2.8 (A4), U3.8 (A4), U4.8 (A4)
/mA7: P8.16, U1.7 (A5), U2.7 (A5), U3.7 (A5), U4.7 (A5)
/mA8: P8.18, U1.6 (A6), U2.6 (A6), U3.6 (A6), U4.6 (A6)
/mA9: P8.20, U1.5 (A7), U2.5 (A7), U3.5 (A7), U4.5 (A7)
/mA10: P8.22, U1.27 (A8), U2.27 (A8), U3.27 (A8), U4.27 (A8)
/mA11: P8.24, U1.26 (A9), U2.26 (A9), U3.26 (A9), U4.26 (A9)
/mA12: P8.26, U1.23 (A10), U2.23 (A10), U3.23 (A10), U4.23 (A10)
/mA13: P8.28, U1.25 (A11), U2.25 (A11), U3.25 (A11), U4.25 (A11)
/mA14: P8.30, U1.4 (A12), U2.4 (A12), U3.4 (A12), U4.4 (A12)
/mA15: P8.32, U1.28 (A13), U2.28 (A13), U3.28 (A13), U4.28 (A13)
/mA16: P8.34, U1.3 (A14), U2.3 (A14), U3.3 (A14), U4.3 (A14)
/mA17: P8.36, U1.31 (A15), U2.31 (A15), U3.31 (A15), U4.31 (A15)
/mA18: P8.38, U1.2 (A16), U2.2 (A16), U3.2 (A16), U4.2 (A16)
/mD0: P8.5, U1.13 (D0)
/mD1: P8.7, U1.14 (D1)
/mD2: P8.9, U1.15 (D2)
/mD3: P8.11, U1.17 (D3)
/mD4: P8.13, U1.18 (D4)
/mD5: P8.15, U1.19 (D5)
/mD6: P8.17, U1.20 (D6)
/mD7: P8.19, U1.21 (D7)
/mD8: P8.21, U2.13 (D0)
/mD9: P8.23, U2.14 (D1)
/mD10: P8.25, U2.15 (D2)
/mD11: P8.27, U2.17 (D3)
/mD12: P8.29, U2.18 (D4)
/mD13: P8.31, U2.19 (D5)
/mD14: P8.33, U2.20 (D6)
/mD15: P8.35, U2.21 (D7)
/mD16: P8.37, U3.13 (D0)
/mD17: P8.39, U3.14 (D1)
/mD18: P9.1, U3.15 (D2)
/mD19: P9.3, U3.17 (D3)
/mD20: P9.5, U3.18 (D4)
/mD21: P9.7, U3.19 (D5)
/mD22: P9.9, U3.20 (D6)
/mD23: P9.11, U3.21 (D7)
/mD24: P9.13, U4.13 (D0)
/mD25: P9.15, U4.14 (D1)
/mD26: P9.17, U4.15 (D2)
/mD27: P9.19, U4.17 (D3)
/mD28: P9.21, U4.18 (D4)
/mD29: P9.23, U4.19 (D5)
/mD30: P9.25, U4.20 (D6)
/mD31: P9.27, U4.21 (D7)
/mmCPLD1_TCK: P11.4, U14.11 (TCK)
/mmCPLD1_TMS: P11.2, U14.10 (TMS)
/mmFPGA_TDI: P11.3, U14.9 (TDI)
/mmFPGA_TDO: P11.1, U14.24 (TDO)
GND: C3.2, C4.2, C6.2, C14.2, C18.2, C24.2, C27.2, C30.2, C34.2, C36.2, C38.2, D1.2 (K), P1.1, P2.1, P3.1, P4.1, P9.39, P9.40, R5.1, R6.1, U1.16 (GND), U2.16 (GND), U3.16 (GND), U4.16 (GND), U7.1 (GND), U14.4 (GND), U14.17 (GND), U14.25 (GND)
unnamed: R3.1, U2.30 (CE2)
unnamed: R2.1, U1.30 (CE2)
unnamed: R4.1, U3.30 (CE2)
unnamed: R7.1, U4.30 (CE2)
unnamed: D5.2 (K), R6.2
unnamed: D6.2 (K), R5.2
unnamed: D1.1 (A), R1.2

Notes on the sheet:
CPLD XC9532XL VQ44
POWER
TO-252
MOUNTING HOLES
LOGOs
OUTPUT FROM CPLD
INPUT to CPLD
Unused CPLD pins
LED's
Signals coming from CPLD for these
I/O from connector to/from CPLD

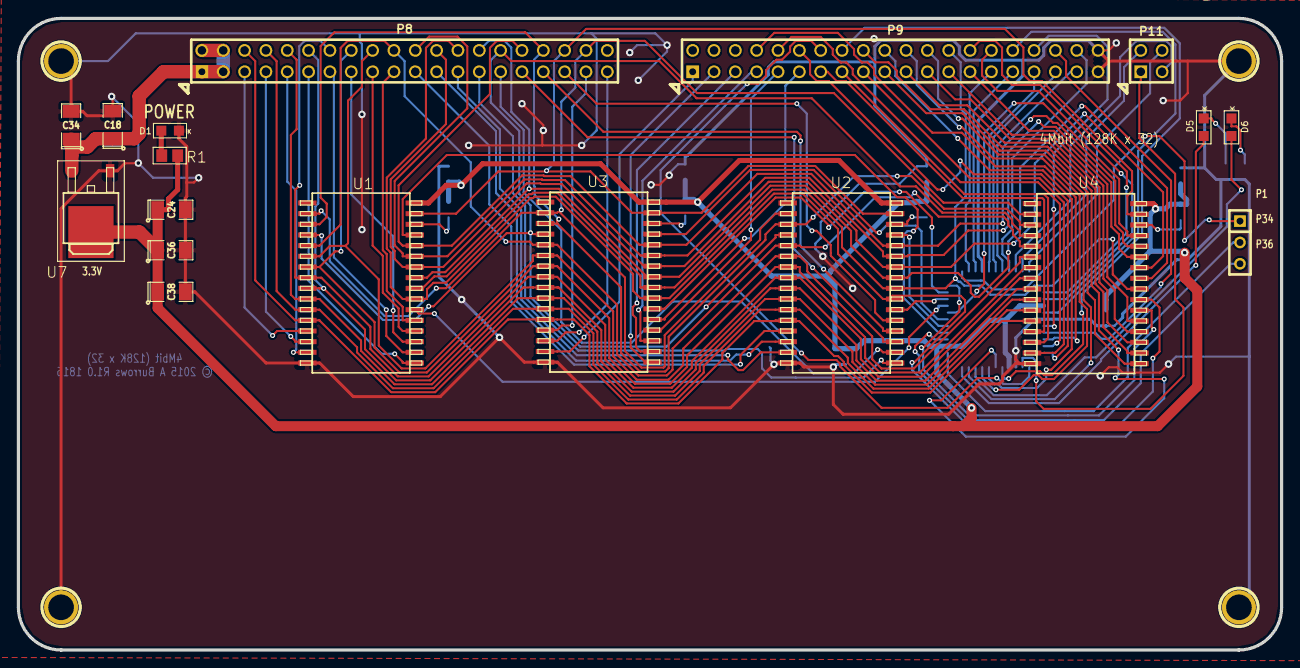
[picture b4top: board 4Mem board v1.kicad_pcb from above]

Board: 2 copper layers, 150.4 x 75.2 mm, 35 parts (0 on the bottom side), 97 nets.
